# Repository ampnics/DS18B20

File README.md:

# D18BS20 — DS18B20 Temperature Sensor Module

> An open-source, minimal DS18B20 1-Wire temperature sensor module with onboard pull-up resistor and decoupling capacitor — designed for the engineering community.

---

## 📺 Video & Course

| Resource | Link |
|---|---|
| 🎬 DS18B20 Temperature Sensor Design | [Watch on YouTube](https://youtu.be/5xwUL280BjY) |
| 📚 Hardware Module Design — Full Playlist | [Watch Playlist](https://youtube.com/playlist?list=PLxgq6Jtu7shSHcKxjR8DUTR9fcr9KYakO&si=6mWbozdvvU1mXMRr) |

---

## 📋 Table of Contents

- [Overview](#-overview)
- [Features](#-features)
- [Schematic](#-schematic)
- [Hardware Specifications](#-hardware-specifications)
- [Pin Description](#-pin-description)
- [Repository Structure](#-repository-structure)
- [Getting Started](#-getting-started)
- [Usage Example](#-usage-example)
- [Contributing](#-contributing)
- [License](#-license)

---

## 🔍 Overview

The **D18BS20** is a minimal, open-source breakout module for the **DS18B20 1-Wire digital temperature sensor**. It includes an onboard **4.7KΩ pull-up resistor** on the data line and a **100nF decoupling capacitor** on the power supply — making it ready to plug directly into any microcontroller without additional external components.

Designed in **KiCad 9.0.1** as part of the *Hardware Module Design* series on YouTube.

---

## ✨ Features

- ✅ DS18B20 1-Wire digital temperature sensor
- ✅ Onboard 4.7KΩ pull-up resistor on DQ line
- ✅ Onboard 100nF decoupling capacitor on VDD
- ✅ 3-pin connector (SIG, GND, VDD) for easy interfacing
- ✅ Compatible with 3.3V and 5V systems
- ✅ Temperature range: -55°C to +125°C
- ✅ ±0.5°C accuracy (-10°C to +85°C)
- ✅ Compact, minimal design
- ✅ Fully open-source — KiCad files included

---

## 📐 Schematic

```
VDD ──┬──── R1 (4K7) ────┬──── J1 Pin 1 (SIG)
      │                  │
      C1 (100nF)         └──── DS18B20 DQ (Pin 2)
      │
     GND ──────────────────── DS18B20 GND (Pin 1)
                               DS18B20 VDD (Pin 3) ── VDD

J1 Connector (Conn_01x03):
  Pin 1 → SIG (DQ Data Line)
  Pin 2 → GND
  Pin 3 → VDD
```

---

## 🔧 Hardware Specifications

| Parameter | Details |
|---|---|
| Sensor | DS18B20 |
| Communication | 1-Wire protocol |
| Supply Voltage | 3.0V – 5.5V |
| Temperature Range | -55°C to +125°C |
| Accuracy | ±0.5°C (-10°C to +85°C) |
| Resolution | 9 to 12-bit (configurable) |
| Pull-up Resistor | 4.7KΩ on DQ line |
| Decoupling Cap | 100nF on VDD |
| Connector | 3-pin 2.54mm pitch header |
| PCB Tool | KiCad 9.0.1 |
| Board Revision | V0.0.1 |

---

## 📌 Pin Description

| Pin | Label | Description |
|---|---|---|
| 1 | SIG | 1-Wire data line (DQ) — connect to MCU GPIO |
| 2 | GND | Ground |
| 3 | VDD | Power supply 3.3V or 5V |

---

## 🚀 Getting Started

### Prerequisites
- [KiCad 9.0.1](https://www.kicad.org/) — to open schematic and PCB files

### Clone the Repository
```bash
git clone https://github.com/ampnics/D18BS20.git
cd D18BS20
```

### Open in KiCad
1. Open KiCad
2. Click **"Open Project"**
3. Select `D18BS20.kicad_pro`

---

## 💻 Usage Example

### Arduino / ESP32

```cpp
#include <OneWire.h>
#include <DallasTemperature.h>

#define SIG_PIN 4  // Connect SIG pin of module to GPIO4

OneWire oneWire(SIG_PIN);
DallasTemperature sensors(&oneWire);

void setup() {
  Serial.begin(115200);
  sensors.begin();
}

void loop() {
  sensors.requestTemperatures();
  float tempC = sensors.getTempCByIndex(0);
  Serial.print("Temperature: ");
  Serial.print(tempC);
  Serial.println(" °C");
  delay(1000);
}
```

### Required Libraries
```
OneWire           → by Paul Stoffregen
DallasTemperature → by Miles Burton
```
Install via **Arduino IDE → Library Manager**

---

## 🏭 Fabrication

Gerber files are available in the `fab/` folder.

| Parameter | Value |
|---|---|
| Layers | 2 |
| Board Thickness | 1.6mm |
| Copper Weight | 1oz |
| Min Trace Width | 0.2mm |
| Surface Finish | HASL / ENIG |

---

## 🤝 Contributing

Contributions are welcome!

1. Fork the repository
2. Create your feature branch: `git checkout -b feature/your-feature`
3. Commit your changes: `git commit -m "hw: your change"`
4. Push: `git push origin feature/your-feature`
5. Open a **Pull Request**

---

## 📄 License

This project is licensed under the **MIT License**.

You are free to use, modify, and distribute this design for personal and commercial purposes with attribution.

---

## 👨‍💻 Designed By

**Md Ammar Maniyar** — [Ampnics](https://github.com/ampnics)

*Engineered in India 🇮🇳*

---

## ⭐ Support the Project

- ⭐ **Star** this repository
- 📺 **Subscribe** to the [YouTube Channel](https://youtube.com/playlist?list=PLxgq6Jtu7shSHcKxjR8DUTR9fcr9KYakO&si=6mWbozdvvU1mXMRr)
- 🍴 **Fork** and contribute back

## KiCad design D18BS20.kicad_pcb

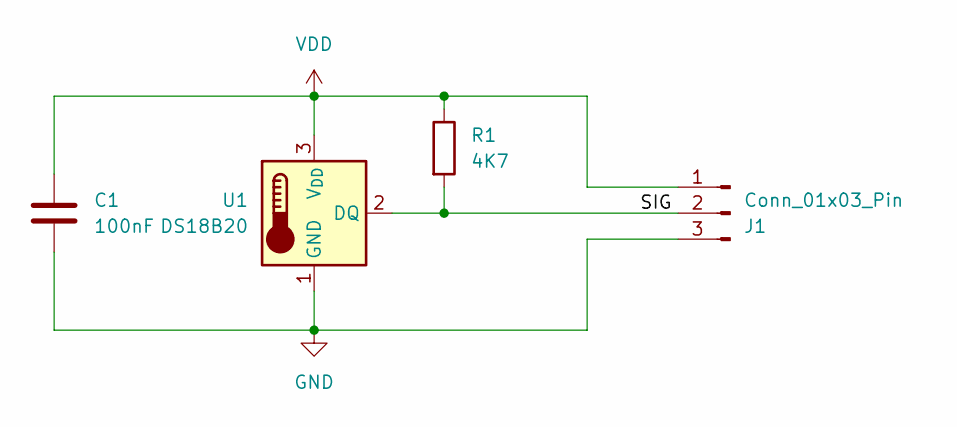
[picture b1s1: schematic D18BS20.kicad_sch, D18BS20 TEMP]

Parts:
C1: 100nF; C_0603_1608Metric
J1: Conn_01x03_Pin; PinHeader_1x03_P2.54mm_Horizontal
R1: 4K7; R_0603_1608Metric
U1: DS18B20; TO-92_W4.0mm_StaggerEven_Horizontal_FlatSideUp

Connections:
/SIG: J1.2, R1.2, U1.2 (DQ)
GND: C1.2, J1.3, U1.1 (GND)
VDD: C1.1, J1.1, R1.1, U1.3 (V_{DD})

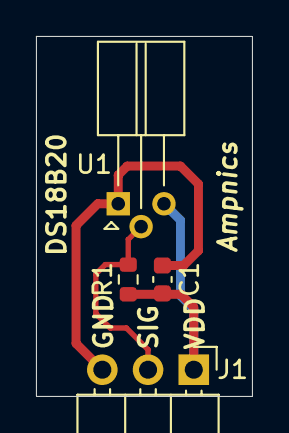
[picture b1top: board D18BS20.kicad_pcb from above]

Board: 2 copper layers, 12.0 x 20.0 mm, 4 parts (0 on the bottom side), 3 nets.

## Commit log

2026-03-15 DS18B20 Temprature Sensor
2026-03-15 Create README.md for D18BS20 Temperature Sensor Module
    Added comprehensive documentation for the D18BS20 temperature sensor module, including features, usage examples, and contribution guidelines.

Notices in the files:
README.md:
License: MIT
